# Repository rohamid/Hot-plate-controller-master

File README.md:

## STM32 PCB Hot Plate soldering controller
STM32 based pcb soldering hot plate controller.

### Hot plate controller Top

### Hot plate controller Bottom

### Hot plate controller Top 

### Hot plate controller Top

### Hot plate controller Top

### Hot plate controller PCB dimension

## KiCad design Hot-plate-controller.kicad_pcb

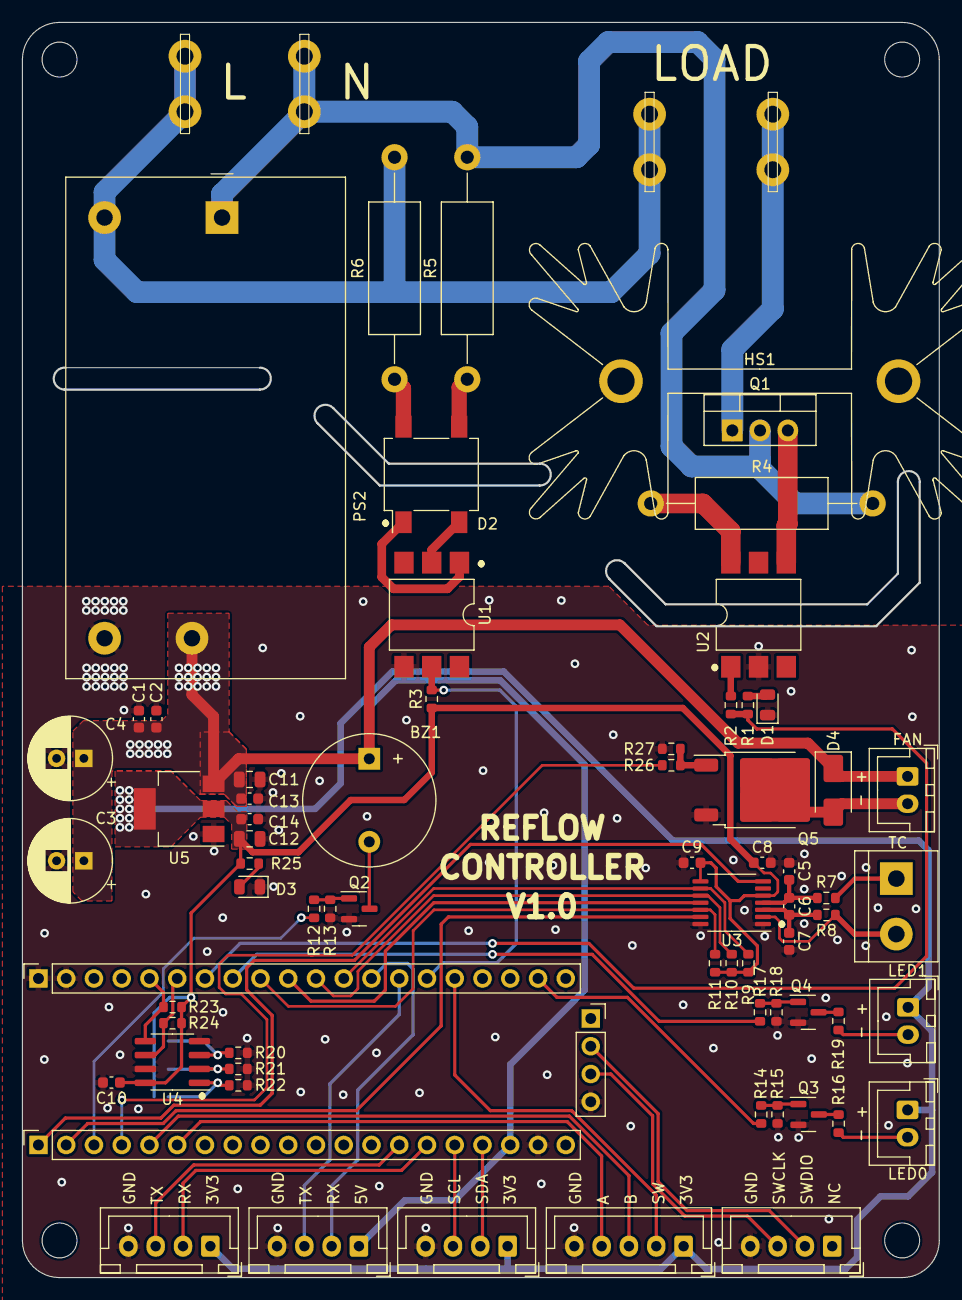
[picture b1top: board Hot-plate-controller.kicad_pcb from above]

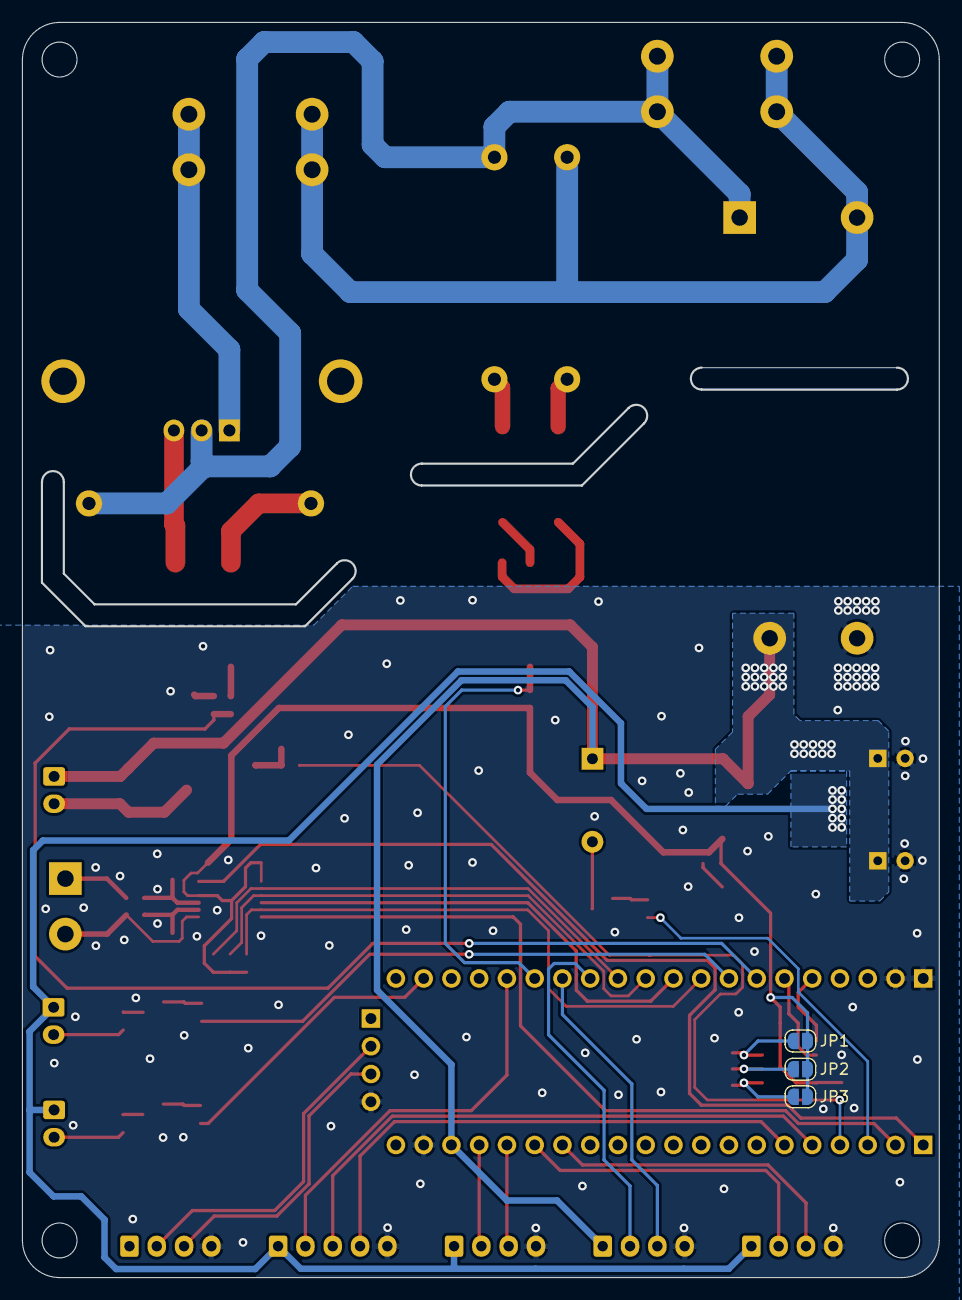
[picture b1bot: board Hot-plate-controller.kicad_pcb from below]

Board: 2 copper layers, 83.8 x 114.8 mm, 81 parts (3 on the bottom side), 57 nets.

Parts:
BZ1: Buzzer; Buzzer_12x9.5RM7.6
C1, C2, C5, C7, C8, C9, C10, C13, C14: 100n; C_0603_1608Metric
C3, C4: 100u; CP_Radial_D7.5mm_P2.50mm
C6: 10n; C_0603_1608Metric
C11: 10u; C_0805_2012Metric
C12: 22u; C_0805_2012Metric
D1: LED; LED_0805_2012Metric
D2: ABS2; Diode_Bridge_Vishay_DFS
D3: RED; LED_0805_2012Metric
D4: 1N4007; D_SMA
H1, H2, H3, H4: MountingHole; MountingHole_3.2mm_M3
HS1: Heatsink; Heatsink_Fischer_SK129-STS_42x25mm_2xDrill2.5mm
J1, J4: LOAD; blade_terminal
J2: AC_N; blade_terminal
J3: AC_L; blade_terminal
J5: J_TC; TerminalBlock_bornier-2_P5.08mm
J6, J7: Conn_01x20; PinSocket_1x20_P2.54mm_Vertical
J8: Conn_01x04; PinSocket_1x04_P2.54mm_Vertical
J9: ENC; JST_XH_B5B-XH-A_1x05_P2.50mm_Vertical
J10: I2C; JST_XH_B4B-XH-A_1x04_P2.50mm_Vertical
J11, J14: SERIAL; JST_XH_B4B-XH-A_1x04_P2.50mm_Vertical
J12, J13: LED_OUT; JST_XH_B2B-XH-A_1x02_P2.50mm_Vertical
J15: STLINK; JST_XH_B4B-XH-A_1x04_P2.50mm_Vertical
J16: FAN; JST_XH_B2B-XH-A_1x02_P2.50mm_Vertical
JP1, JP2, JP3: JMP; SolderJumper-2_P1.3mm_Open_RoundedPad1.0x1.5mm
PS2: IRM-10-5; Converter_ACDC_MeanWell_IRM-10-xx_THT
Q1: BTA16-800BW; TO-220-3_Vertical
Q2, Q3, Q4: MMBT3904; SOT-23
Q5: MJD122T4; TO-252-2
R1: 330R; R_0603_1608Metric
R2: 470R; R_0603_1608Metric
R3, R9, R10, R11, R13, R15, R18, R20, R21, R22, R27: 10K; R_0603_1608Metric
R4: 1K; R_Axial_DIN0414_L11.9mm_D4.5mm_P20.32mm_Horizontal
R5, R6: 33K; R_Axial_DIN0414_L11.9mm_D4.5mm_P20.32mm_Horizontal
R7, R8: 100R; R_0603_1608Metric
R12, R14, R16, R17, R19, R25, R26: 1K; R_0603_1608Metric
R23, R24: 2K2; R_0603_1608Metric
U1: 4N25; SMDIP-6_W9.53mm
U2: MOC3021M; SMDIP-6_W9.53mm
U3: MAX31856; TSSOP-14_4.4x5mm_P0.65mm
U4: CAT24C128; SOIC-8_3.9x4.9mm_P1.27mm
U5: AMS1117-3.3; SOT-223-3_TabPin2

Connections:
+3V3: C8.1, C9.1, C10.1, C12.1, C14.1, J9.1, J10.1, J11.1, J12.1, J13.1, JP1.2 (B), JP2.2 (B), JP3.2 (B), R3.1, R9.1, R10.1, R11.1, R23.2, R24.2, R25.2, U3.5 (AVDD), U3.8 (DVDD), U4.8 (VCC), U5.2 (VO)
+5V: BZ1.1 (-), C1.1, C2.1, C3.1, C4.1, C11.1, C13.1, D4.1 (K), J6.18, J14.1, J16.1, PS2.4 (+Vo), U5.3 (VI)
/A: J6.6, J9.4
/A0: J7.16, J9.2
/A1: J7.15, R3.2, U1.5
/A2: J7.14, J14.3
/A3: J7.13, J14.2
/A4: J7.12, R9.2, U3.9 (~CS)
/A5: J7.11, R10.2, U3.10 (SCK)
/A6: J7.10, U3.11 (SDO)
/A7: J7.9, R11.2, U3.12 (SDI)
/A8: J6.5, J9.3
/B0: J7.8, R17.1
/B1: J7.7, R1.1, R2.1
/B6: J6.14, J11.3
/B7: J6.15, J11.2
/B8: J6.16, J10.3
/B9: J6.17, J10.2
/B10: J7.6, R24.1, U4.6 (SCL)
/B11: J7.5, R23.1, U4.5 (SDA)
/B12: J6.1, U3.7 (~DRDY)
/B13: J6.2, U3.13 (~FAULT)
/B14: J6.3, R12.1
/B15: J6.4, R26.1
/C13: J7.19, R14.1
/CLK: J8.3, J15.3
/DIO: J8.2, J15.2
GND: C1.2, C2.2, C3.2, C4.2, C5.2, C7.2, C8.2, C9.2, C10.2, C11.2, C12.2, C13.2, C14.2, D1.1 (K), D3.1 (K), J6.19, J7.1, J7.2, J8.4, J9.5, J10.4, J11.4, J14.4, J15.4, PS2.3 (-Vo), Q2.2 (E), Q3.2 (E), Q4.2 (E), Q5.3 (E), R13.1, R15.1, R18.1, R20.1, R21.1, R22.1, R27.1, U1.4, U2.2, U3.1 (AGND), U3.14 (DGND), U4.4 (GND), U4.7 (WP), U5.1 (GND)
unnamed: BZ1.2 (+), Q2.3 (C)
unnamed: D1.2 (A), R1.2
unnamed: D2.1 (+), U1.1
unnamed: D2.2 (-), U1.2
unnamed: D2.3, R5.1
unnamed: D2.4, R6.1
unnamed: D3.2 (A), R25.1
unnamed: D4.2 (A), J16.2, Q5.2 (C)
unnamed: J1.1, J2.1, PS2.2 (AC/L), R6.2
unnamed: J3.1, PS2.1 (AC/N), Q1.2 (A2), R4.2, R5.2
unnamed: J4.1, Q1.1 (A1)
unnamed: J5.1, R7.1
unnamed: J5.2, R8.1, U3.2 (BIAS)
unnamed: J12.2, R16.2
unnamed: J13.2, R19.2
unnamed: JP1.1 (A), R20.2, U4.3 (A2)
unnamed: JP2.1 (A), R21.2, U4.2 (A1)
unnamed: JP3.1 (A), R22.2, U4.1 (A0)
unnamed: Q1.3 (G), U2.4
unnamed: Q2.1 (B), R12.2, R13.2
unnamed: Q3.1 (B), R14.2, R15.2
unnamed: Q3.3 (C), R16.1
unnamed: Q4.1 (B), R17.2, R18.2
unnamed: Q4.3 (C), R19.1
unnamed: Q5.1 (B), R26.2, R27.2
unnamed: R2.2, U2.1
unnamed: R4.1, U2.6
unnamed: C5.1, C6.1, R7.2, U3.4 (T+)
unnamed: C6.2, C7.1, R8.2, U3.3 (T-)
